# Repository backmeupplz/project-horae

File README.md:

# Project Horae

A miniaturized successor to [Watchy](https://watchy.sqfmi.com/), the open-source ESP32 e-paper watch. It's rebuilt as thin as possible, in a slim band form factor (think Fitbit Charge, not a square).

Build log: **[projecthorae.com](https://projecthorae.com)**

## Build one
- [ORDER.md](ORDER.md): the JLCPCB order (files and every order-form setting), the shopping list with Canadian sources, and the totals
- [ASSEMBLY.md](ASSEMBLY.md): printing, a test-print checklist, bench bring-up, assembly, the dock wiring, and the firmware rules the hardware depends on
- [hardware/README.md](hardware/README.md): the board design, the pre-order review, what to verify at bring-up, and the cost

## Research
- [Displays](research/displays.md): bar-shaped e-paper and memory LCD panels
- [Batteries](research/batteries.md): thin LiPo, sodium-ion reality check, power budget
- [Electronics](research/electronics.md): EDA tools, fabs shipping to Vancouver, key ICs
- [CAD & printing](research/cad-tools.md): code-CAD and the headless Bambu A1 mini pipeline
- [Prototype v0](research/prototyping.md): breadboard kit, steps, charging
- [Build plan, rev A](research/build-plan.md): custom board straight away, order → solder → firmware → case → wear

## 3D explorer
The landing page's interactive model (`explorer/`) is generated from the case CAD and the KiCad board:
`.venv/bin/python cad/web.py` (needs Docker for KiCad and `npx` for gltf-transform). Re-run it after changing the CAD or the board.

## Printing (Bambu A1 mini, 0.4 nozzle, one filament per job)
- `cad/out/plates/petg.3mf`: both shells plus the dock's tray and lid, in PETG Basic or Matte. Use 0.1 mm layers **and a 0.1 mm first layer** (it is the skin over the watch's magnets), no supports.
- `cad/out/plates/tpu.3mf`: every seal and cushion plus the dock's grip pad, in TPU 90A (not 95A: twice as stiff) from the external spool, printed slowly. Give the bezel gasket 0.08 mm layers.
- Carbon-fibre version: print `petg-cf.3mf` (PETG-CF, hardened nozzle) and `petg-cf-set.3mf` (the colour-matched PETG parts) instead of `petg.3mf`.
- Per-part notes (orientation, layer heights, squeeze) are in `PRINT` in `cad/horae.py`, and a full `.venv/bin/python cad/horae.py` run prints them.

## Adding a timeline entry
The timeline is newest first. Add a new `<li class="entry">` block at the top of the `<ol class="timeline">` in `index.html`, and put its photos in `media/YYYY-MM-DD/`.

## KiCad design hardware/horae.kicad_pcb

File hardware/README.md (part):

# Horae rev A hardware

ESP32-S3 band watch board: **33.6 × 16.0 × 0.6 mm, 4 layers**. JLCPCB assembles it (Standard PCBA, top side only) in a
1-up 70 × 70 mm frame.
- **Case:** 35.6 × 18.0 × 6.80 mm, smaller than a Fitbit Charge 3 (38 × 18.3 × 11.8) in every direction. Two PETG shells
  click together with no glue (see `../cad/horae.py`).
- **Board fit:** the board sits 0.2 mm off every cavity wall, because JLC routes outlines to ±0.2 mm. Six crush ribs in the
  case centre it.

**Status (2026-10-06): pre-order review done, not ordered.**
- **Review:** four parallel reviews (schematic and parts, layout and fab files, size, sourcing) found 7 blockers. All are
  fixed and listed below.
- **Checks:** ERC 0. DRC 0 errors, 0 warnings, 0 unconnected. A probe of JLC's multilayer limits is clean: minimum
  clearance 0.110, track 0.100, hole-to-copper 0.235, copper-to-edge 0.201 mm.
- **Reproducible:** a fresh build gives the same board and CPL byte for byte.
- **Ordering:** [../ORDER.md](../ORDER.md). **Assembly and bring-up:** [../ASSEMBLY.md](../ASSEMBLY.md).

Everything here is generated from two files:
- [`design.py`](design.py), the netlist
- [`../spec.py`](../spec.py), the shared dimensions

## Rebuild
```sh
./build.sh       # ~6 min: schematic, ERC, placement, staged Freerouting, pours, DRC, STEP, gerbers, BOM/CPL, panel, renders
python3 cost.py  # live JLC parts (with JLC's attrition/minimums) + Standard PCBA fees -> out/cost.json; `cost.py 5` for 5 boards
```
It needs:
- Docker: it runs KiCad 10 from the official `kicad/kicad:10.0` image through `./kicad`.
- A Java 25 runtime.
- The Freerouting 2.4.1 jar in `~/.local`.

| File | What |
|---|---|
| `design.py` | parts, LCSC numbers, pin-to-net map |
| `gen_sch.py` | writes `horae.kicad_sch` (symbols joined by net labels) |
| `gen_pcb.py` | outline, stack, pinned and legalized placement (the build fails on any drift over 1 mm), net classes, keep-outs; exports the Specctra DSN |
| `stage.py`, `dsn_only.py`, `sesfix.py` | staged routing: touch first, then the e-paper bus, then the rest; deterministic (seeded UUIDs, one router thread) |
| `route.py` | imports the Freerouting session, pours GND, adds stitching and the RF via fence, removes unused escape vias |
| `fab.py` | `out/jlc-bom.csv` and `out/jlc-cpl.csv` (gerber coordinates, JLC rotation offsets) |
| `panel.py` | the 70 × 70 mm frame: `out/panel-gerbers.zip`, `out/jlc-cpl-panel.csv`, `out/panel-top.png` |
| `cost.py` | JLC cost estimate from the BOM |
| `lib/` | symbols, footprints and 3D models: LCSC-imported, TI/Espressif land patterns, Watchy's antenna |
| `rf/` | openEMS antenna model and match fitting |
| `out/` | schematic PDF, STEP, gerbers, BOM, CPL, panel, ERC/DRC reports, renders |

## Design summary
- **MCU:** ESP32-S3FN8 (8 MB in-package flash).
  - 40 MHz KYX crystal (12 pF, ±10 ppm) with Espressif's 24 nH series L on XTAL_P.
  - The exposed pad follows Espressif's land pattern: solid copper, nine 1.0 mm mask windows, 12 vias in the mask webs,
    and no vias in the paste.
  - **Timekeeping:** a 32.768 kHz crystal on GPIO15/16 drives the ESP32's own RTC, as on Watchy v3 and Yatchy, so there's
    no RTC chip. ±20 ppm is about 1 min/month before the phone sync corrects it. All four crystal load caps are 18 pF C0G.
  - **Antenna:** Watchy's meander IFA, trimmed 6.64 mm, ending 0.35 mm from the board edge. It is fed by a 50 Ω GCPW
    (0.15 mm track, 0.15 mm gap). Match **C11 0.5 pF / L3 0.8 nH**; C12 is not fitted and is the spare tuning spot.
  - **Antenna simulation (v4, this board):** S11 across 2.40–2.48 GHz is −8.8 to −14.2 dB in the case and −8.6 to
    −13.6 dB on the wrist, with a worst in-band loss of 0.78 dB.
  - The re-layout put ground closer to the feed, which lowered the resonance 0.6–0.8 %. So L3 went from 1.2 to 0.8 nH,
    the most robust match across JLC's parts. `rf/results/report_v4_trim6.64.txt` has the details.
- **Power:**
  - **Pogo pads:** 4 on the bottom for the charging/USB dock, whose spring pins reach them through the case floor. They are
    VBUS + D− on one side and GND + D+ on the other. ST's USBLC6-2P6 sits flow-through between the pads and the ESP32.
  - **TI BQ25101** linear charger (1.6 × 0.9 mm WCSP):
    - charges at 20 mA (6.8 kΩ ISET, 0.5C for a 40 mAh cell), with TI's ISET RC (2.7 kΩ + 10 nF) for currents under
      50 mA;
    - 4.7 µF/25 V on IN and 1 µF on OUT, both at the chip;
    - ≤ 75 nA battery drain.
    - The IN pin is rated 30 V, but the USBLC6 clamps VBUS from about 6 V, so the input is 5 V only.
  - **TI TPS62840** buck:
    - 60 nA quiescent, 3.3 V set by a 267 kΩ VSET resistor (TI's window is 256–278 kΩ);
    - 2.2 µH LSCND1608 inductor (1.3 A saturation, 0.2 Ω, 0.8 mm).
  - **Battery voltage:** a 10 MΩ / 10 MΩ ±1 % divider (0.2 µA) with 100 nF at the ADC. Calibrate each board at the
    4.20 V end of charge.
  - **Soldered parts:** the battery goes to a **square + pad (TP5)** and a **round − pad (TP6)** on the bottom; the motor
    to 1.5 mm pads.
- **Sensors:** ST LIS2DUX12 accelerometer (pedometer at 2.7 µA, tap, wake-up, 6D, ML core).
  - **I²C:** address **0x19**, on GPIO8 (SDA) / GPIO9 (SCL) with the ESP32's internal pull-ups, so 100 kHz.
  - **Interrupts:** INT1/INT2 on GPIO10/11.
  - **Layout:** nothing on any layer under it (ST TN0018).
- **Display:** GDEM0097T61 into a Hirose FH34SRJ-18S.
  - **Connector:** its slot and fitting nails face the ribbon's U-bend at −X, and **pad = 19 − display pin**.
  - **Booster:** Good Display's reference (p.20) in tiny packages:
    - 47 µH Sunlord SWPA3010S (3 × 3 × 1.0 mm) with 10 µF at its input;
    - Nexperia PMZ390UN switch (30 V);
    - 3× Nexperia PMEG3002AEL Schottky (30 V, about 6× less leakage than the PMEG3005EL);
    - 2.2 Ω sense;
    - 2.2 µF/25 V on the ±15–20 V rails (0402 parts lose about 90 % of their capacitance there) and 1 µF/25 V on the rest.
- **Touch:** 4 capacitive electrodes (4.0 × 1.6 mm) along the long edges, on touch channels GPIO1–4, each through a
  510 Ω series resistor at the chip. No buttons.
  - On every layer, no other trace and no ground pour come within 0.5 mm of an electrode.
  - The electrodes are well below Espressif's recommended size (8 mm+), so measure raw counts in the closed case first
    (bring-up checks).
- **Haptics:** 6 mm coin ERM (Vybronics VC0625B001L, 2.5 mm, 10 mm leads) on a PMZ390UN low-side switch, with a
  PMEG3002AEL flyback diode. It is rated 2.5 V, so firmware drives it with PWM.
- **Mic:** LMD2718T261 top-port PDM mic: DATA on GPIO38, CLK on GPIO39, and powered from GPIO40 (0 µA when off).
  - The ROM drives GPIO40 high in USB-OTG download mode, so it may only be the mic's supply.
  - Burn `DIS_USB_OTG_DOWNLOAD_MODE` at the first flash.
- **Height:** the tallest parts are J1 (1.0 mm, 1.1 max) and L4 (1.0 mm). Then come the mic (0.9, 1.0 max), the ESP32
  (0.885), L5 (0.8) and the accelerometer (0.74). The display sits 1.05 mm above the board.

### GPIO plan
| Side of U1 | GPIO | Use |
|---|---|---|
| facing the antenna (pins 6–14) | 1, 2, 3, 4 | touch DOWN, BACK, MENU, UP (each through 510 Ω) |
| | 5 | vibration motor (PWM) |
| | 6 | charger CHG (open drain, low = charging: wakes the watch on the dock) |
| | 7 | battery ADC (ADC1 channel 6) |
| | 8, 9 | I²C SDA, SCL (accelerometer, 0x19) |
| facing the display connector (pins 15–27) | 10, 11 | accelerometer INT1, INT2 |
| | 12, 13, 14, 17, 18, 21 | display BUSY, RES, DC, CS, SCK, MOSI |
| | 15, 16 | 32.768 kHz crystal |
| | 19, 20 | USB D−, D+ (dock pads, through the USBLC6) |
| bottom (pins 43–45) | 38, 39, 40 | mic DATA, CLK, power |
| test pads (bottom) | 0, 43, 44, EN, 3.3 V | BOOT, TXD0, RXD0, reset, supply |

Every display, I²C, touch and wake line is on an RTC GPIO (0–21), so the ULP core can redraw the minutes without waking
the main CPU (Yatchy's biggest battery win). The ULP bit-bangs I²C: its hardware I²C pins are GPIO0–3.

## Pre-order review (2026-10-06): what changed
- **Blockers fixed:**
  - **J1 faced the wrong way.** The FH34SRJ's slot is on the fitting-nail side, so the ribbon couldn't reach it. J1 is
    turned around with its pins remapped. It also moved 1.7 mm toward +X, because Good Display's bend rule (R > 0.5 mm)
    with the 11.18 mm tail needs that much room.
  - **CPL:** it was relative to the board centre, while the gerbers use absolute coordinates, so every part would have
    landed about 141 mm off. U4 also needed a rotation offset; the CPL now has offsets for U4 and L4.
  - **WCSP lands:** the U2/U3 ball pads (0.185–0.2 mm, mask = pad) were below JLC's minimum. They are now TI's 0.23 mm
    NSMD lands with 0.25 mm square paste.
  - **Touch:** foreign traces ran under the electrodes on the inner and bottom layers.
  - **RF:** the RF match pads were 0.07 mm apart, which would merge the solder mask and tombstone L3.
  - **Thermal vias:** the ESP32's exposed pad had open vias inside the paste.
  - **Panel:** JLC Standard PCBA needs a panel of at least 70 × 70 mm. JLC's own 2 × 4 panel would have meant paying for
    16 assembled boards, so `panel.py` makes a 1-up frame.
- **Should-fix items done:**
  - **Vias:** all are now 0.45/0.2 mm. 0.4 mm pads cost about $36 more per order and triggered 4-wire testing.
  - **Supplies:** 0.2–0.3 mm traces; VDD3P3 on the top layer with no vias.
  - **Decoupling:** every cap within 1 mm of its pin, with new caps at VDD3P3_CPU, VDDA, the booster input and the charger
    output.
  - **Crystals:** on the top layer at their pins, with nothing underneath.
  - **USB ESD:** flow-through.
  - **Mic:** its pins are swapped so the ROM can't back-drive it during flashing.
  - **Lower-leakage diodes, and rail caps that keep their value at 20 V.**
  - **Genuine ST USBLC6.**
  - **Parts with better stock:** the original Sunlord inductor, plus ±1 % 10 MΩ and 510 Ω resistors with no 6,000-piece
    minimums.
  - **Silkscreen:** pin-1 and cathode marks for JLC's placement check.
  - **Paste:** reduced on the FPC connector. Thermal spokes on the non-critical 0201s against tombstoning.

## Verify at bring-up
1. **RF:** the in-case and on-wrist responses sit about 100 MHz apart, so a ±3 % resonance error costs about 4 dB at one
   band edge.
   - The steel spring bar is part of the antenna's environment. Keep it within ±1 mm of 2.15 mm past the case end, or
     re-run `rf/`.
   - Verify on the first boards with a VNA through a pigtail at the C11 pad (cut the trace to U1). Close the case and
     measure with the strap on, off and on a wrist, then retune C11/L3; C12 is the spare.
   - A bare board always reads high, so test it in the case.
2. **Touch:** read raw counts and noise in the closed case before relying on touch as the only input.
3. **Booster:** SSD1680's current-sense trip on RESE isn't published, so L4's saturation margin (0.22 A rated, 0.35 A
   typical) is unknown. Probe RESE (current = V / 2.2 Ω) and watch the VGH ramp.
4. **Crystals:**
   - The 40 MHz must be within ±10 ppm: trim C1/C2 with a TX tone if not.
   - Check that the 32 kHz crystal starts. Its 70 kΩ resistance is at Espressif's limit, and the firmware falls back to
     the internal RC clock.
5. **Charger:** it can't run the board without a cell, and its 10-hour timer stops charging if the watch stays awake on
   the dock. Bring the board up from a bench supply on TP5/TP6, and deep-sleep while docked.
6. **JLC preview:** order with "Confirm Parts Placement" and check every pin-1 dot and cathode bar against the
   silkscreen, especially U1–U4, U6, J1, Q1/Q2, D1–D4, MIC1 and Y1.
7. **Recovery without buttons:** EN, BOOT (GPIO0), TXD0/RXD0 and 3.3 V are on bottom test pads, and USB is on the dock
   pads.

## Cost (JLC Standard PCBA, live 2026-10-06; `python3 cost.py`)
| Item (USD) | 2 boards | 5 boards |
|---|---|---|
| Bare PCB: 5 frames, 4 layers, 0.6 mm, ENIG, JLC04061H-3313 stack-up (impedance control not needed), 0.45/0.2 vias, plugged | 46.20 | 46.20 |
| PCBA setup 25.56 + stencil 8.21 + 33 feeders × 1.53 + fixtures 16.42 + X-ray + placement confirmation and packing | 118.03 | 122.13 |
| Parts, with JLC's attrition and minimum quantities | 30.42 | 62.93 |
| Joints (about 230 per board × $0.0016) | ~0.75 | ~1.85 |
| **Subtotal** | **≈ 195** | **≈ 233** |
| DHL Express (2–4 business days); Global Standard is capped at $99 orders | 31.23 | 31.23 |

- **Import:** duty 0 % (HS 8534.00.00). GST + BC PST 12 % is collected at delivery, plus DHL's CAD 18 clearance fee.
  There is no DDP option for Canada.
- **Fees:** on Standard PCBA every BOM line pays the $1.53 feeder fee, basic or extended alike. JLC has no basic or
  preferred 0201 parts, so swapping parts for basic ones saves nothing here; only fewer lines do.
- **Pre-buy the ESP32-S3FN8:** JLC has 602 in stock and 0 at LCSC. Buy 5–10 into your JLC parts inventory before
  ordering.

## Battery and motor (bought separately, soldered: 4 joints)
- **Cell:** a 3.0 mm LiPo with protection (PCM), at most 21.4 × 16.0 × 3.25 mm including the PCM. The PCM end may be up
  to 3.5 thick and 2.5 long.
  - Buy cells no thicker than 3.05 mm, and measure them on arrival: thickness tolerance is often ±0.3.
  - Real capacity in this pocket is **40–55 mAh** (301518 / 301519 / 301520 class).
  - They ship with two bare wire leads (no plug): trim them, then red to + and black to −.
  - **Thinner option:** a bare 2.5 mm cell (LP251320, 40 mAh, buyable at quantity 1) would make the case 6.30 mm. It would
    need cell protection on the board and an RF retune.
- **Motor:** Vybronics VC0625B001L, a 6 × 2.5 mm brushed coin ERM with 10 mm leads (Digi-Key 1670-VC0625B001L-ND). No
  6 mm motor with spring contacts exists off the shelf.
- **Why not a plug:** a JST SH socket, the plug and its lead slack need about 2 mm more case length, and the board's bottom
  side would need assembly too. Two pads take seconds to solder.

## Charging dock (bought parts; the tray, lid and grip pad print with the case)
- **Spring pins:** 4 Mill-Max 0955-0-15-20-71-14-11-0 (plus 2 spares). Docked, each presses about 42 g on its pad.
- **Magnets:** 4 × 3 × 3 mm N52 in the dock; the case holds 2 × 3 × 1 mm N52.
  - Placed end for end, the watch is pushed off, so VBUS never lands on GND.
  - They hold 1.9× the pins' spring force.
  - The case's magnets click into the bottom shell from the inside, behind a 0.1 mm skin, so lifting the watch off can't
    pull them out.
- **USB-C:** [Adafruit 6050](https://www.adafruit.com/product/6050) sunken breakout. Its 5.1 kΩ CC pull-downs make any
  USB-C charger give 5 V, and D+/D− are broken out for flashing.
- **Wire:** 2–3 cm each of 30 AWG for VBUS, GND, D+ and D− (twist D+ with D−). These 4 wires are the dock's only soldering.
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
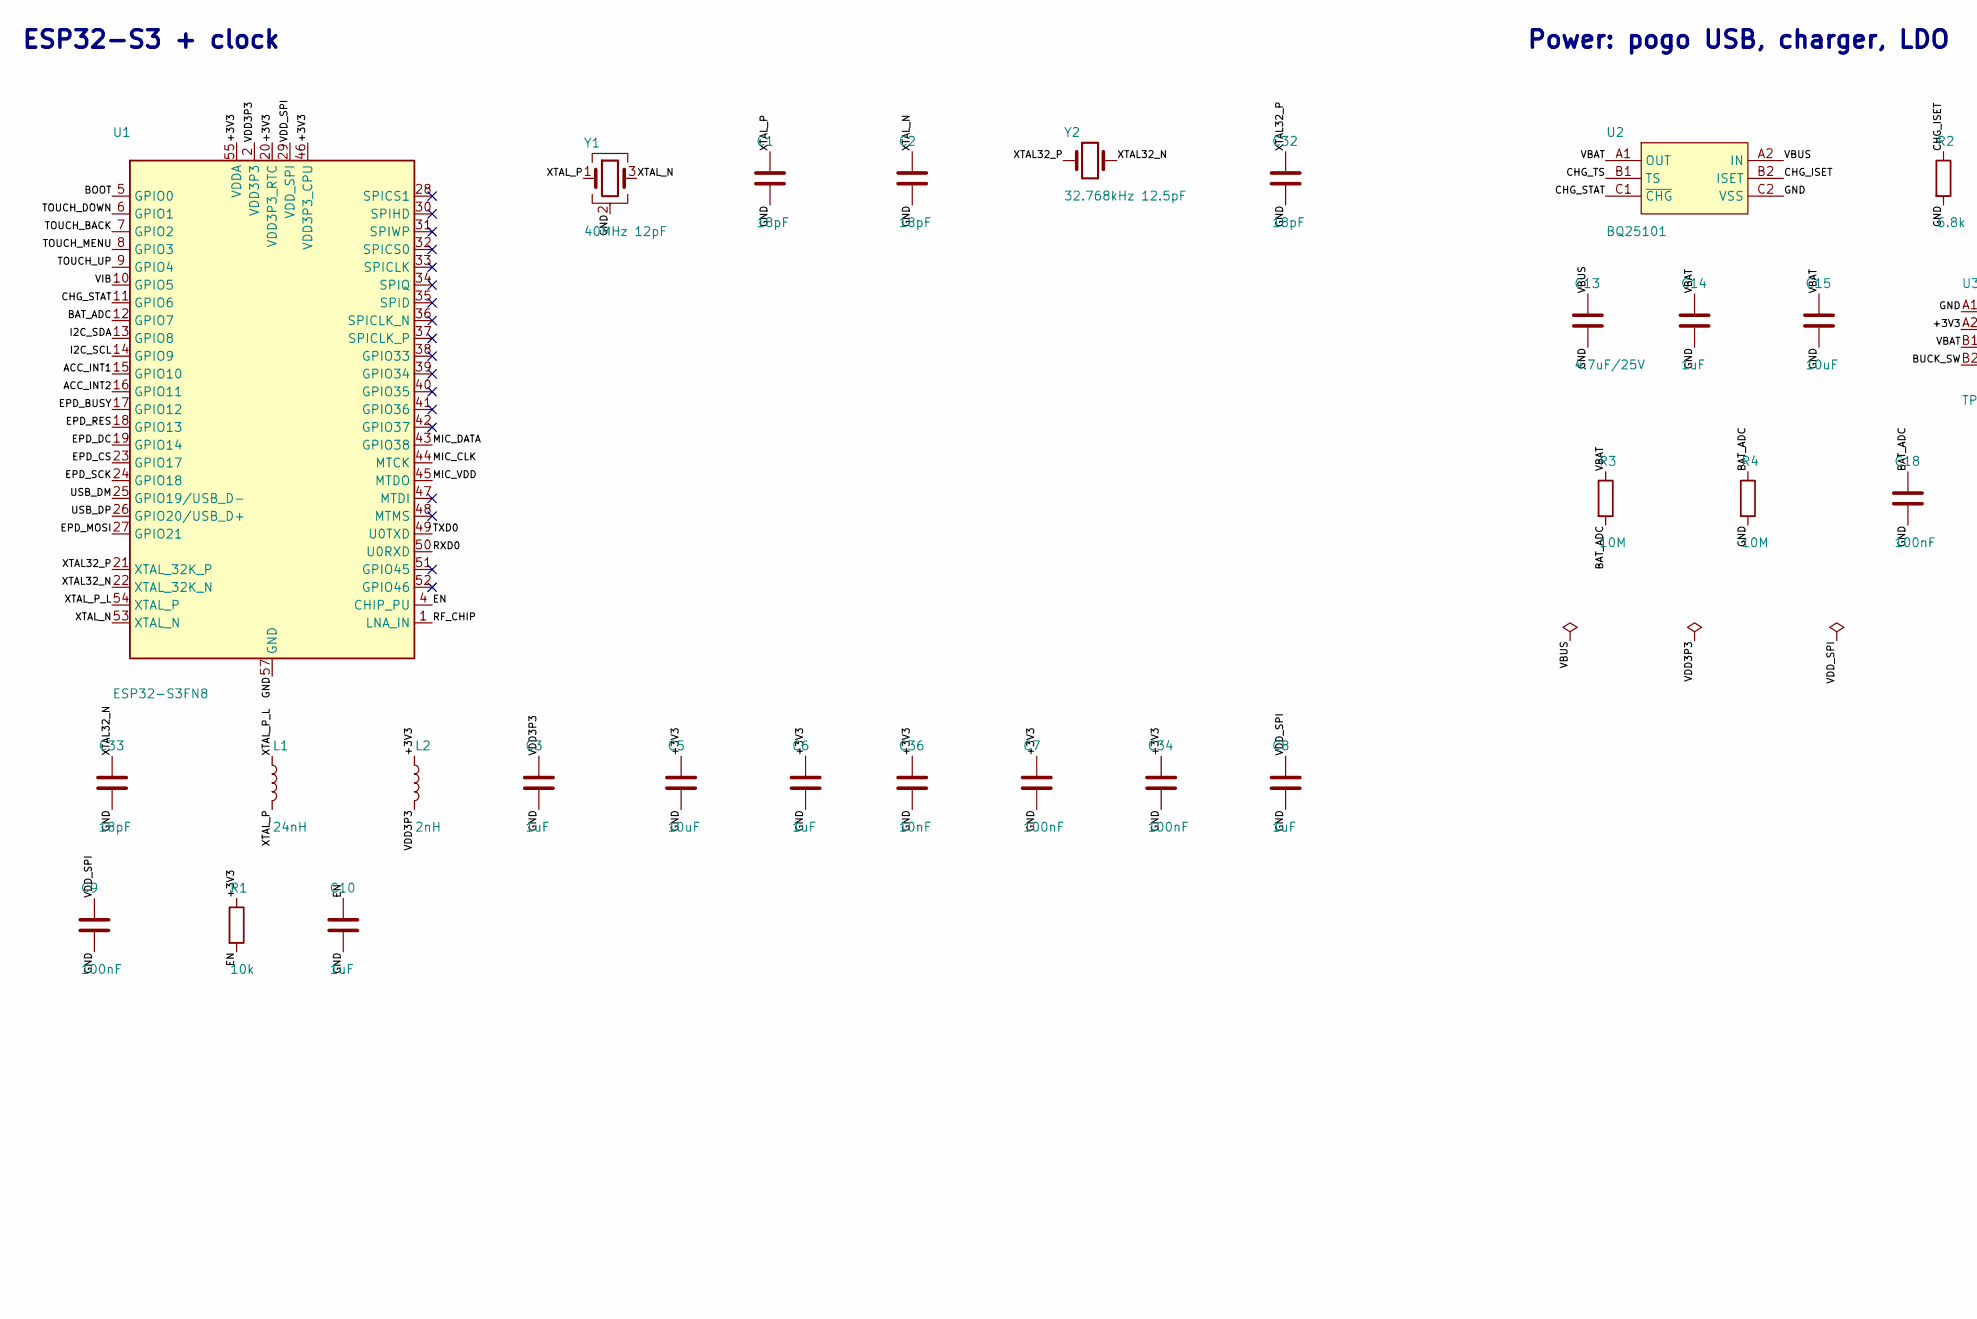
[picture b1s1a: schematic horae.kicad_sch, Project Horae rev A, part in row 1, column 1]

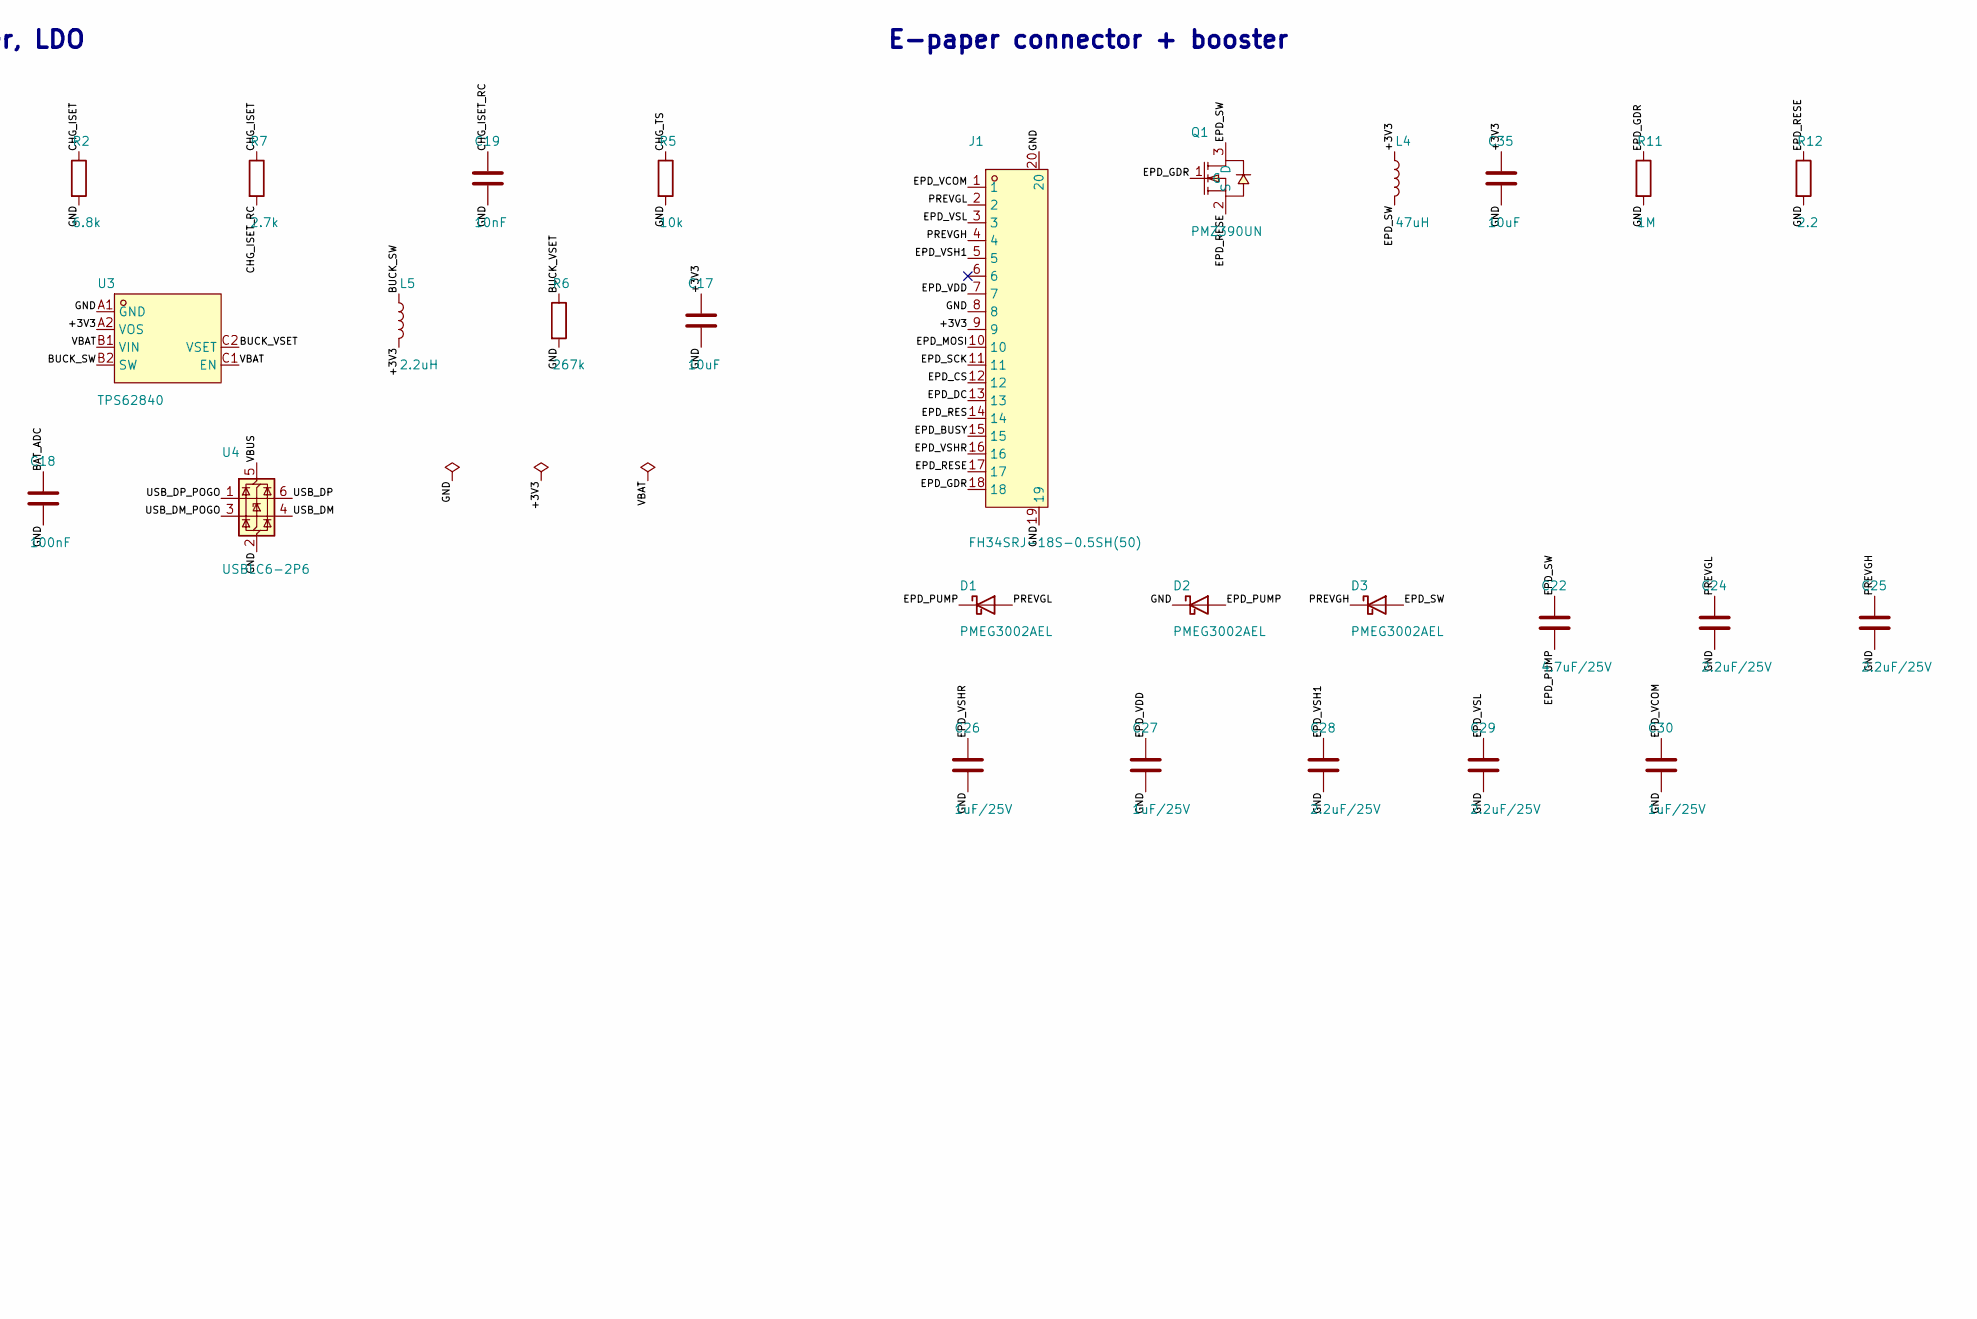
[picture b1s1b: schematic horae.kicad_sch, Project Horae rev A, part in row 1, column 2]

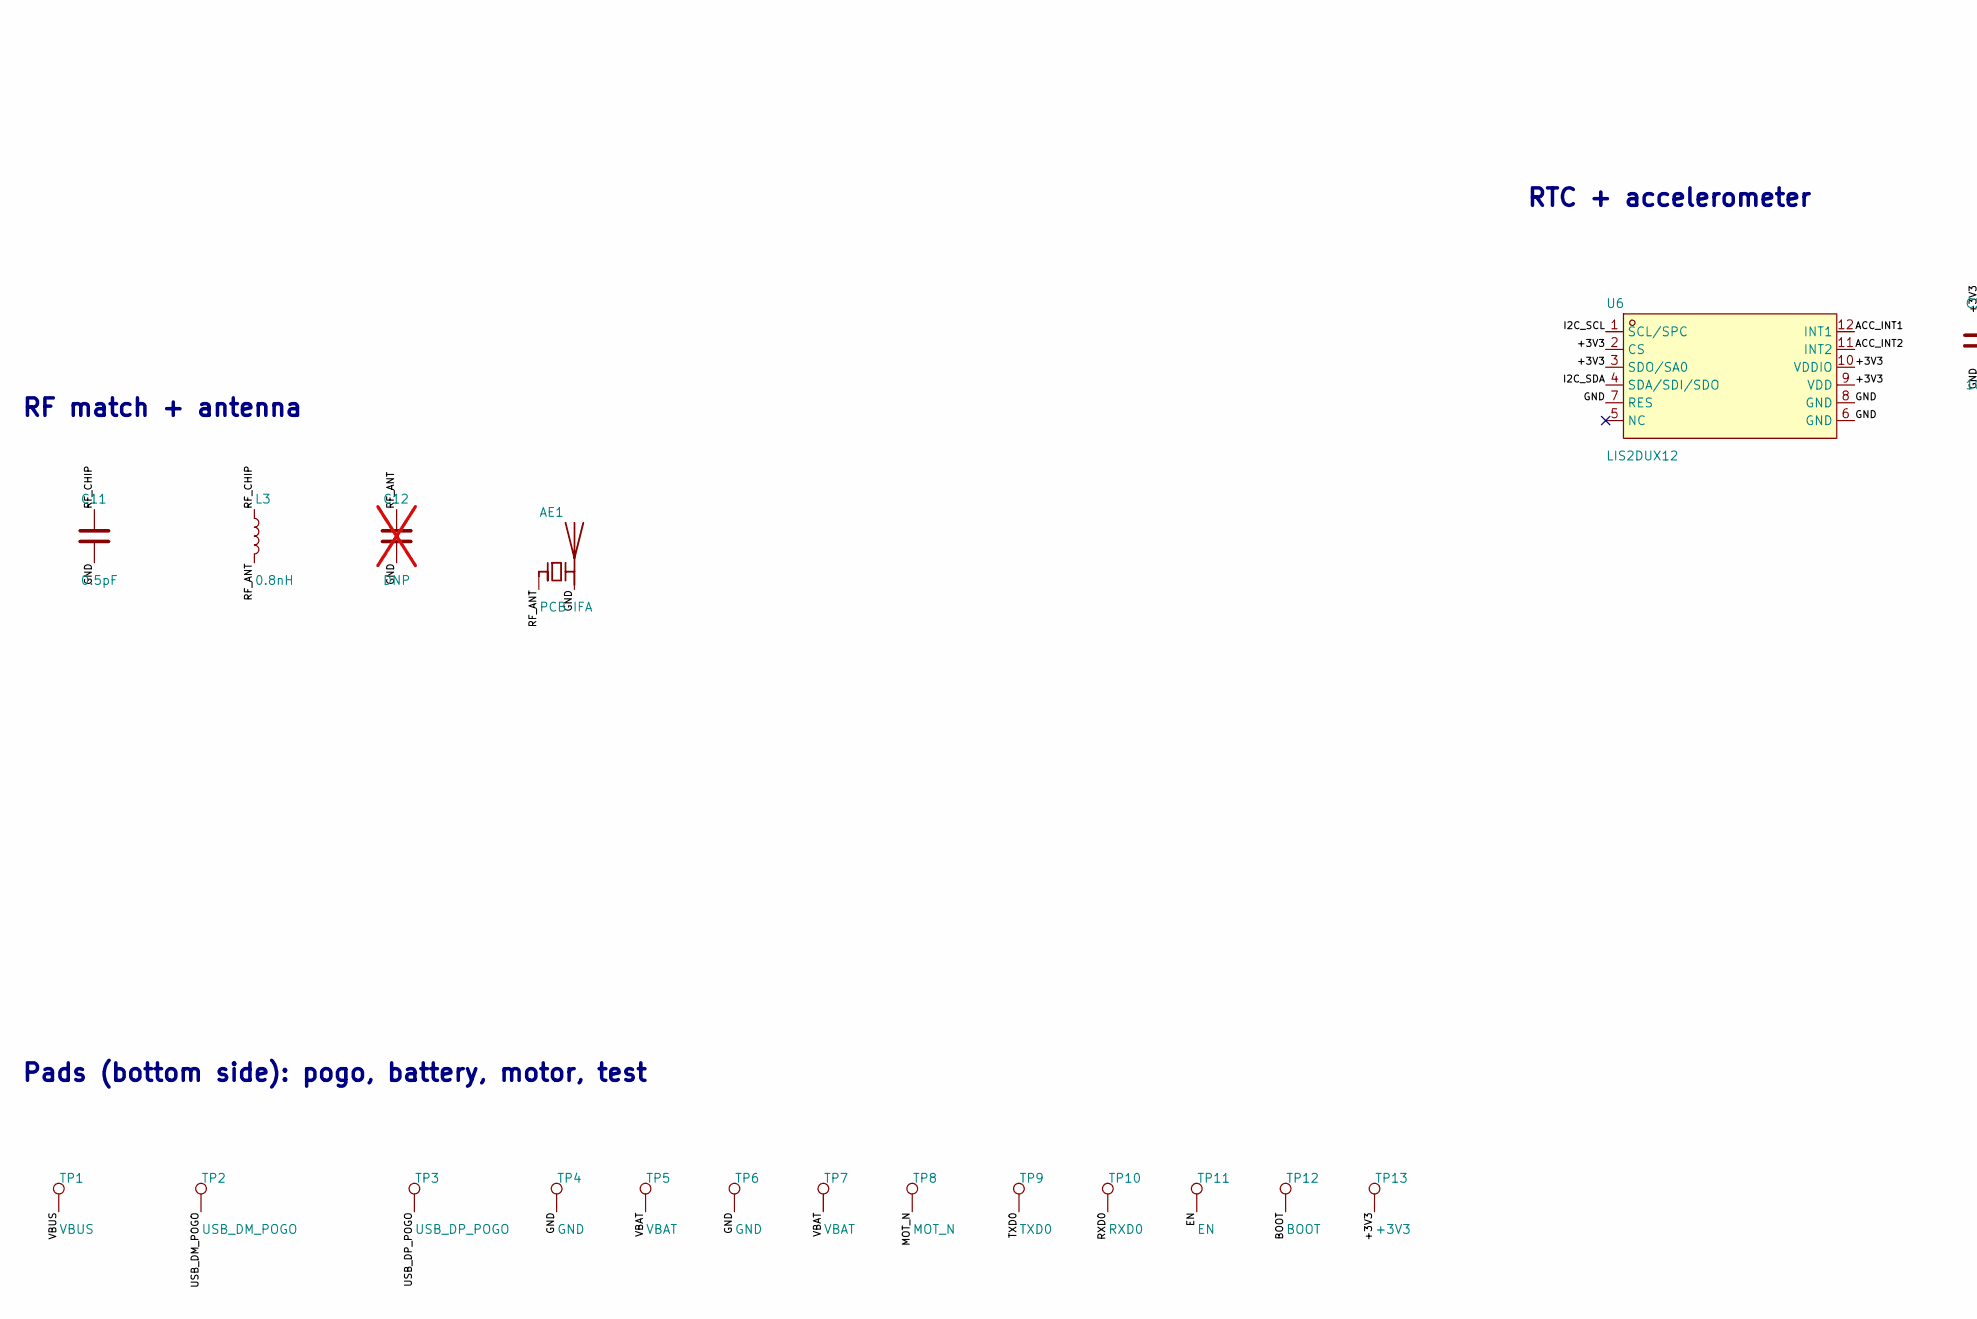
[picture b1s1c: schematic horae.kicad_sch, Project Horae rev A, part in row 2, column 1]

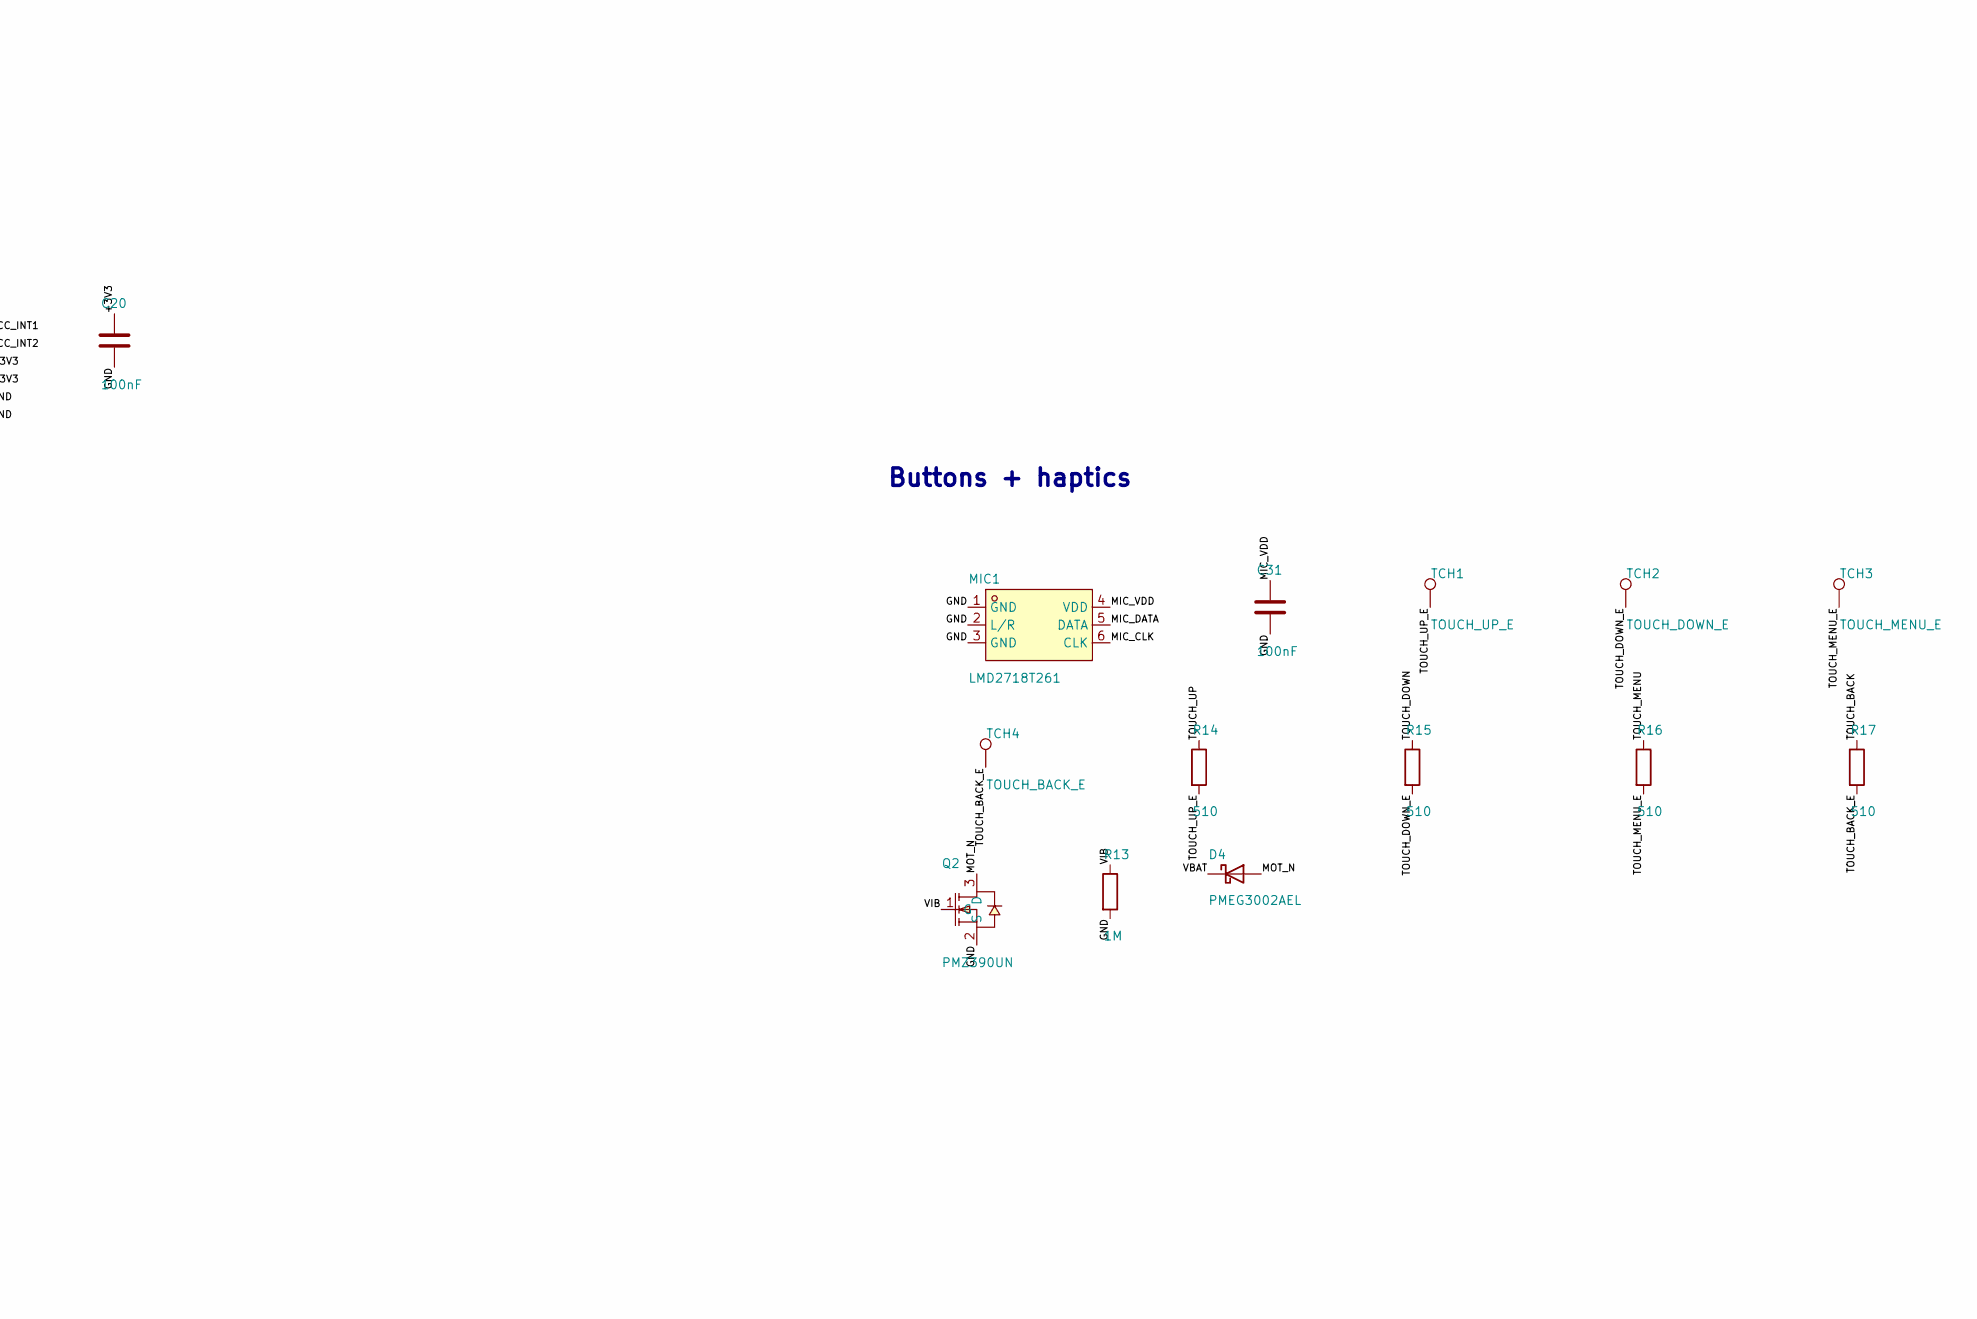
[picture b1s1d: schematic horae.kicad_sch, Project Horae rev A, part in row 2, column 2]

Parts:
AE1: PCB IFA; SWRA117D
C1, C2, C32, C33: 18pF; C_0201_0603Metric; LCSC C62164
C3, C6, C8, C10, C14: 1uF; C_0201_0603Metric; LCSC C76935
C5, C15, C17, C35: 10uF; C_0402_1005Metric; LCSC C15525
C7, C9, C18, C20, C31, C34: 100nF; C_0201_0603Metric; LCSC C66938
C11: 0.5pF; C_0201_0603Metric; LCSC C85920
C12: DNP; C_0201_0603Metric; not fitted
C13, C22: 4.7uF/25V; C_0402_1005Metric; LCSC C2858031
C19, C36: 10nF; C_0201_0603Metric; LCSC C326875
C24, C25, C28, C29: 2.2uF/25V; C_0402_1005Metric; LCSC C307418
C26, C27, C30: 1uF/25V; C_0402_1005Metric; LCSC C52923
D1, D2, D3, D4: PMEG3002AEL; SOD-882_L1.0-W0.6-RD; LCSC C478015
J1: FH34SRJ-18S-0.5SH(50); FFC-SMD_18P-P0.50_FH34SRJ-18S-0.5SH; LCSC C3169386
L1: 24nH; L_0201_0603Metric; LCSC C2991767
L2: 2nH; L_0201_0603Metric; LCSC C86125
L3: 0.8nH; L_0201_0603Metric; LCSC C156227
L4: 47uH; IND-SMD_L3.0-W3.0_SWPA3010S; LCSC C96826
L5: 2.2uH; IND-SMD_L1.6-W0.8; LCSC C31123918
MIC1: LMD2718T261; MIC-SMD_6P-L2.8-W1.9-P0.98-TL; LCSC C5373237
Q1, Q2: PMZ390UN; SOT-883-3_L1.0-W0.6-BR; LCSC C458236
R1, R5: 10k; R_0201_0603Metric; LCSC C473048
R2: 6.8k; R_0201_0603Metric; LCSC C274877
R3, R4: 10M; R_0201_0603Metric; LCSC C3036920
R6: 267k; R_0201_0603Metric; LCSC C423627
R7: 2.7k; R_0201_0603Metric; LCSC C273271
R11, R13: 1M; R_0201_0603Metric; LCSC C295786
R12: 2.2; R_0402_1005Metric; LCSC C327251
R14, R15, R16, R17: 510; R_0201_0603Metric; LCSC C304550
TCH1: TOUCH_UP_E; TouchPad_4.0x1.6mm
TCH2: TOUCH_DOWN_E; TouchPad_4.0x1.6mm
TCH3: TOUCH_MENU_E; TouchPad_4.0x1.6mm
TCH4: TOUCH_BACK_E; TouchPad_4.0x1.6mm
TP1: VBUS; TestPoint_Pad_D1.0mm
TP2: USB_DM_POGO; TestPoint_Pad_D1.0mm
TP3: USB_DP_POGO; TestPoint_Pad_D1.0mm
TP4: GND; TestPoint_Pad_D1.0mm
TP5: VBAT; TestPoint_Pad_2.0x2.0mm
TP6: GND; TestPoint_Pad_D2.0mm
TP7: VBAT; TestPoint_Pad_D1.5mm
TP8: MOT_N; TestPoint_Pad_D1.5mm
TP9: TXD0; TestPoint_Pad_D1.0mm
TP10: RXD0; TestPoint_Pad_D1.0mm
TP11: EN; TestPoint_Pad_D1.0mm
TP12: BOOT; TestPoint_Pad_D1.0mm
TP13: +3V3; TestPoint_Pad_D1.0mm
U1: ESP32-S3FN8; QFN-56-1EP_7x7mm_P0.4mm_EP4x4mm_Espressif; LCSC C2913196
U2: BQ25101; DSBGA-6_L0.9-W1.6-R2-C3-P0.40-BL; LCSC C478468
U3: TPS62840; DSBGA-6_L1.4-W1.0-R2-C3-P0.40-BL; LCSC C2071139
U4: USBLC6-2P6; SOT-666; LCSC C15999
U6: LIS2DUX12; LGA-12_L2.0-W2.0-P0.50-TL_LIS2DUX12TR; LCSC C17548754
Y1: 40MHz 12pF; Crystal_SMD_2520-4Pin_2.5x2.0mm; LCSC C19076867
Y2: 32.768kHz 12.5pF; CRYSTAL-SMD_L2.1-W1.2-P1.50; LCSC C403709

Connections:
+3V3: C5.1, C6.1, C7.1, C17.1, C20.1, C34.1, C35.1, C36.1, J1.9, L2.1, L4.1, L5.2, R1.1, TP13.1, U1.20 (VDD3P3_RTC), U1.46 (VDD3P3_CPU), U1.55 (VDDA), U1.56 (VDDA), U3.A2 (VOS), U6.2 (CS), U6.3 (SDO/SA0), U6.9 (VDD), U6.10 (VDDIO)
ACC_INT1: U1.15 (GPIO10), U6.12 (INT1)
ACC_INT2: U1.16 (GPIO11), U6.11 (INT2)
BAT_ADC: C18.1, R3.2, R4.1, U1.12 (GPIO7)
BOOT: TP12.1, U1.5 (GPIO0)
BUCK_SW: L5.1, U3.B2 (SW)
BUCK_VSET: R6.1, U3.C2 (VSET)
CHG_ISET: R2.1, R7.1, U2.B2 (ISET)
CHG_ISET_RC: C19.1, R7.2
CHG_STAT: U1.11 (GPIO6), U2.C1 (~CHG)
CHG_TS: R5.1, U2.B1 (TS)
EN: C10.1, R1.2, TP11.1, U1.4 (CHIP_PU)
EPD_BUSY: J1.15, U1.17 (GPIO12)
EPD_CS: J1.12, U1.23 (GPIO17)
EPD_DC: J1.13, U1.19 (GPIO14)
EPD_GDR: J1.18, Q1.1 (G), R11.1
EPD_MOSI: J1.10, U1.27 (GPIO21)
EPD_PUMP: C22.2, D1.1 (K), D2.2 (A)
EPD_RES: J1.14, U1.18 (GPIO13)
EPD_RESE: J1.17, Q1.2 (S), R12.1
EPD_SCK: J1.11, U1.24 (GPIO18)
EPD_SW: C22.1, D3.2 (A), L4.2, Q1.3 (D)
EPD_VCOM: C30.1, J1.1
EPD_VDD: C27.1, J1.7
EPD_VSH1: C28.1, J1.5
EPD_VSHR: C26.1, J1.16
EPD_VSL: C29.1, J1.3
GND: AE1.2 (PCB_Trace), C1.2, C2.2, C3.2, C5.2, C6.2, C7.2, C8.2, C9.2, C10.2, C11.2, C12.2, C13.2, C14.2, C15.2, C17.2, C18.2, C19.2, C20.2, C24.2, C25.2, C26.2, C27.2, C28.2, C29.2, C30.2, C31.2, C32.2, C33.2, C34.2, C35.2, C36.2, D2.1 (K), J1.8, J1.19, J1.20, MIC1.1 (GND), MIC1.2 (L/R), MIC1.3 (GND), Q2.2 (S), R2.2, R4.2, R5.2, R6.2, R11.2, R12.2, R13.2, TP4.1, TP6.1, U1.57 (GND), U2.C2 (VSS), U3.A1 (GND), U4.2 (GND), U6.6 (GND), U6.7 (RES), U6.8 (GND), Y1.2 (G), Y1.4 (G)
I2C_SCL: U1.14 (GPIO9), U6.1 (SCL/SPC)
I2C_SDA: U1.13 (GPIO8), U6.4 (SDA/SDI/SDO)
MIC_CLK: MIC1.6 (CLK), U1.44 (MTCK)
MIC_DATA: MIC1.5 (DATA), U1.43 (GPIO38)
MIC_VDD: C31.1, MIC1.4 (VDD), U1.45 (MTDO)
MOT_N: D4.2 (A), Q2.3 (D), TP8.1
PREVGH: C25.1, D3.1 (K), J1.4
PREVGL: C24.1, D1.2 (A), J1.2
RF_ANT: AE1.1 (FEED), C12.1, L3.2
RF_CHIP: C11.1, L3.1, U1.1 (LNA_IN)
RXD0: TP10.1, U1.50 (U0RXD)
TOUCH_BACK: R17.1, U1.7 (GPIO2)
TOUCH_BACK_E: R17.2, TCH4.1
TOUCH_DOWN: R15.1, U1.6 (GPIO1)
TOUCH_DOWN_E: R15.2, TCH2.1
TOUCH_MENU: R16.1, U1.8 (GPIO3)
TOUCH_MENU_E: R16.2, TCH3.1
TOUCH_UP: R14.1, U1.9 (GPIO4)
TOUCH_UP_E: R14.2, TCH1.1
TXD0: TP9.1, U1.49 (U0TXD)
USB_DM: U1.25 (GPIO19/USB_D-), U4.4 (I/O2)
USB_DM_POGO: TP2.1, U4.3 (I/O2)
USB_DP: U1.26 (GPIO20/USB_D+), U4.6 (I/O1)
USB_DP_POGO: TP3.1, U4.1 (I/O1)
VBAT: C14.1, C15.1, D4.1 (K), R3.1, TP5.1, TP7.1, U2.A1 (OUT), U3.B1 (VIN), U3.C1 (EN)
VBUS: C13.1, TP1.1, U2.A2 (IN), U4.5 (VBUS)
VDD3P3: C3.1, L2.2, U1.2 (VDD3P3), U1.3 (VDD3P3)
VDD_SPI: C8.1, C9.1, U1.29 (VDD_SPI)
VIB: Q2.1 (G), R13.1, U1.10 (GPIO5)
XTAL32_N: C33.1, U1.22 (XTAL_32K_N), Y2.2
XTAL32_P: C32.1, U1.21 (XTAL_32K_P), Y2.1
XTAL_N: C2.1, U1.53 (XTAL_N), Y1.3
XTAL_P: C1.1, L1.2, Y1.1
XTAL_P_L: L1.1, U1.54 (XTAL_P)

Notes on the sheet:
ESP32-S3 + clock
RF match + antenna
Power: pogo USB, charger, LDO
RTC + accelerometer
E-paper connector + booster
Buttons + haptics
Pads (bottom side): pogo, battery, motor, test

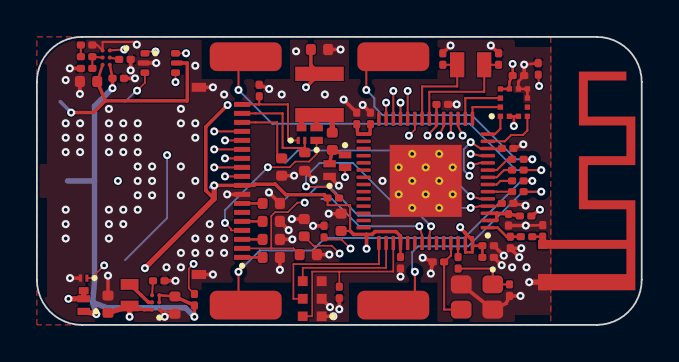
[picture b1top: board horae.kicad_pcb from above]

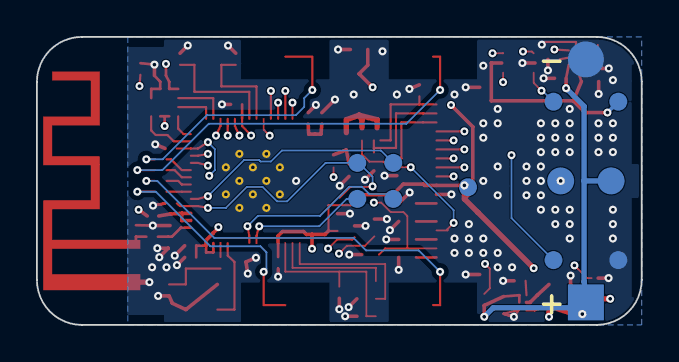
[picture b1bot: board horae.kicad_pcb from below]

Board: 4 copper layers, 33.6 x 16.0 mm, 84 parts (13 on the bottom side), 62 nets.

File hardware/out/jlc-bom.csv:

Comment,Designator,Footprint,LCSC Part #
ESP32-S3FN8,U1,QFN-56-1EP_7x7mm_P0.4mm_EP4x4mm_Espressif,C2913196
40MHz 12pF,Y1,Crystal_SMD_2520-4Pin_2.5x2.0mm,C19076867
18pF,"C1,C2,C32,C33",C_0201_0603Metric,C62164
32.768kHz 12.5pF,Y2,CRYSTAL-SMD_L2.1-W1.2-P1.50,C403709
24nH,L1,L_0201_0603Metric,C2991767
2nH,L2,L_0201_0603Metric,C86125
1uF,"C3,C6,C8,C10,C14",C_0201_0603Metric,C76935
10uF,"C5,C15,C17,C35",C_0402_1005Metric,C15525
10nF,"C36,C19",C_0201_0603Metric,C326875
100nF,"C7,C34,C9,C18,C20,C31",C_0201_0603Metric,C66938
10k,"R1,R5",R_0201_0603Metric,C473048
0.5pF,C11,C_0201_0603Metric,C85920
0.8nH,L3,L_0201_0603Metric,C156227
BQ25101,U2,DSBGA-6_L0.9-W1.6-R2-C3-P0.40-BL,C478468
6.8k,R2,R_0201_0603Metric,C274877
2.7k,R7,R_0201_0603Metric,C273271
4.7uF/25V,"C13,C22",C_0402_1005Metric,C2858031
TPS62840,U3,DSBGA-6_L1.4-W1.0-R2-C3-P0.40-BL,C2071139
2.2uH,L5,IND-SMD_L1.6-W0.8,C31123918
267k,R6,R_0201_0603Metric,C423627
10M,"R3,R4",R_0201_0603Metric,C3036920
USBLC6-2P6,U4,SOT-666,C15999
LIS2DUX12,U6,LGA-12_L2.0-W2.0-P0.50-TL_LIS2DUX12TR,C17548754
FH34SRJ-18S-0.5SH(50),J1,FFC-SMD_18P-P0.50_FH34SRJ-18S-0.5SH,C3169386
PMZ390UN,"Q1,Q2",SOT-883-3_L1.0-W0.6-BR,C458236
47uH,L4,IND-SMD_L3.0-W3.0_SWPA3010S,C96826
1M,"R11,R13",R_0201_0603Metric,C295786
2.2,R12,R_0402_1005Metric,C327251
PMEG3002AEL,"D1,D2,D3,D4",SOD-882_L1.0-W0.6-RD,C478015
2.2uF/25V,"C24,C25,C28,C29",C_0402_1005Metric,C307418
1uF/25V,"C26,C27,C30",C_0402_1005Metric,C52923
LMD2718T261,MIC1,MIC-SMD_6P-L2.8-W1.9-P0.98-TL,C5373237
510,"R14,R15,R16,R17",R_0201_0603Metric,C304550

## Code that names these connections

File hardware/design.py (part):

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
ESP_PINS = {
    "1": "RF_CHIP", "2": "VDD3P3", "3": "VDD3P3", "4": "EN",
    "5": "BOOT",          # GPIO0 strap: test pad only
    # side facing the antenna (pins 6-14, GPIO1-9): touch, interrupts, haptics, ADC - all RTC GPIOs (deep-sleep wake)
    "6": "TOUCH_DOWN",    # GPIO1  T1
    "7": "TOUCH_BACK",    # GPIO2  T2
    "8": "TOUCH_MENU",    # GPIO3  T3
    "9": "TOUCH_UP",      # GPIO4  T4
    "10": "VIB",          # GPIO5   haptic motor
    "11": "CHG_STAT",     # GPIO6   charger CHG (open drain, low = charging): wake on dock
    "12": "BAT_ADC",      # GPIO7   ADC1_CH6
    "13": "I2C_SDA",      # GPIO8   the accelerometer sits right above these two: I2C runs straight up to its south pads ...
    "14": "I2C_SCL",      # GPIO9   (ULP bit-bangs I2C on any RTC GPIO)
    # side facing the display connector (pins 15-27): SPI + I2C on RTC GPIOs so the ULP core can refresh the time alone
    "15": "ACC_INT1",     # GPIO10  ... and the interrupts straight east to its west pads; step/tap wake
    "16": "ACC_INT2",     # GPIO11
    "17": "EPD_BUSY",     # GPIO12
    "18": "EPD_RES",      # GPIO13
    "19": "EPD_DC",       # GPIO14
    "20": "+3V3",         # VDD3P3_RTC
    "21": "XTAL32_P",     # GPIO15  32.768 kHz crystal: the ESP32 RTC keeps time (no RTC IC; phone sync corrects drift)
    "22": "XTAL32_N",     # GPIO16
    "23": "EPD_CS",       # GPIO17
    "24": "EPD_SCK",      # GPIO18
    "25": "USB_DM", "26": "USB_DP",
    "27": "EPD_MOSI",     # GPIO21
    "43": "MIC_DATA",     # GPIO38  PDM data in (the ROM drives GPIO38 LOW in USB-OTG download mode: harmless on an input)
    "44": "MIC_CLK",      # GPIO39  PDM clock (I2S0 PDM RX); low in download mode = mic asleep
    "45": "MIC_VDD",      # GPIO40  powers the mic directly: 0 uA when off. MTDO is driven HIGH by the ROM in USB-OTG download
                          #         mode (TRM v1.8 Table 33.4-2), so it may only be the mic's VDD, never its DATA output
    "29": "VDD_SPI", "46": "+3V3", "49": "TXD0", "50": "RXD0",
    "53": "XTAL_N", "54": "XTAL_P_L", "55": "+3V3", "56": "+3V3", "57": "GND",
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    # --- sensors ---
    ("U6", "horae:LIS2DUX12TR", "LIS2DUX12", "horae:LGA-12_L2.0-W2.0-P0.50-TL_LIS2DUX12TR", "C17548754",
     {"1": "I2C_SCL", "2": "+3V3", "3": "+3V3", "4": "I2C_SDA", "6": "GND", "7": "GND", "8": "GND", "9": "+3V3",
      "10": "+3V3", "11": "ACC_INT2", "12": "ACC_INT1"}, "sensors"),   # CS=VDDIO -> I2C, SA0=VDDIO -> 0x19 (ties to the CS pin next to it); DS14071 Table 1: pin 5 NC, pin 7 RES/EXT_CLK to GND
    C("C20", "100nF", C100N, "+3V3", "GND", "sensors"),
    # I2C (accelerometer only) uses the ESP32 internal pull-ups (~45k): ~0.6 us rise at 100 kHz on this short bus

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    TP("TCH1", "TOUCH_UP_E", "horae:TouchPad_4.0x1.6mm", "ui"), TP("TCH2", "TOUCH_DOWN_E", "horae:TouchPad_4.0x1.6mm", "ui"),
    TP("TCH3", "TOUCH_MENU_E", "horae:TouchPad_4.0x1.6mm", "ui"), TP("TCH4", "TOUCH_BACK_E", "horae:TouchPad_4.0x1.6mm", "ui"),
    *[R(r, "510", R510, n, n + "_E", "ui") for r, n in (("R14", "TOUCH_UP"), ("R15", "TOUCH_DOWN"),
                                                             ("R16", "TOUCH_MENU"), ("R17", "TOUCH_BACK"))],   # HDG 1.3.14: 510R within 1 mm of the pin
    ("Q2", "horae:PMZ390UN,315", "PMZ390UN", "horae:SOT-883-3_L1.0-W0.6-BR", "C458236",
     {"1": "VIB", "2": "GND", "3": "MOT_N"}, "ui"),            # coin ERM low-side switch (~80 mA)
    R("R13", "1M", R1M, "VIB", "GND", "ui"),                     # gate pull-down: motor off while the ESP32 boots
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
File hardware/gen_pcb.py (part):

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        pp(ref, "1", p29[0] + dx, p29[1] - 0.55, "-y")
        track("VDD_SPI", [p29, (p29[0] + tx, p29[1]), pad_xy(fps[ref], "1")], 0.2)

    # --- 40 MHz crystal (Espressif HDG 1.4.3): L1 straight off pin 54, crystal ~1.4 mm out, XTAL_P east of it, XTAL_N round
    # its west side, load caps at the crystal ends; F.Cu only, no vias, nothing under it
    p53, p54 = up(53), up(54)
    pp("L1", "1", p54[0], p54[1] + 0.78, "+y")
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                      (u64[0], p13[1] - 0.6), u64], 0.12)
    y2x, y2y = up(15)[0] - 0.1, -6.45
    put(fps["Y2"], y2x, y2y, 0)
    if pad_xy(fps["Y2"], "1")[0] < pad_xy(fps["Y2"], "2")[0]:   # XTAL32_P (pin 21, east of 22) on the east pad
        put(fps["Y2"], y2x, y2y, 180)
    y2a, y2b = pad_xy(fps["Y2"], "1"), pad_xy(fps["Y2"], "2")
    pp("C32", "1", y2a[0] + 0.8, y2a[1], "-y")              # GND pads to the free board edge
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    track("ACC_INT1", [p15, (p15[0], pad_xy(fps["U6"], "12")[1]), pad_xy(fps["U6"], "12")], 0.12)
    track("ACC_INT2", [p16, (p16[0], pad_xy(fps["U6"], "11")[1]), pad_xy(fps["U6"], "11")], 0.12)
    p12 = up(12)
    pp("C18", "1", p12[0] + 0.78, p12[1], "+x")               # BAT_ADC filter (0.5 s with the divider) at the ADC pin
    track("BAT_ADC", [p12, pad_xy(fps["C18"], "1")], 0.12)

    # --- display booster (GD p.20): L4 between TCH3 and TCH1 with its quiet +3V3 pad between the electrodes and the SW pad
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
